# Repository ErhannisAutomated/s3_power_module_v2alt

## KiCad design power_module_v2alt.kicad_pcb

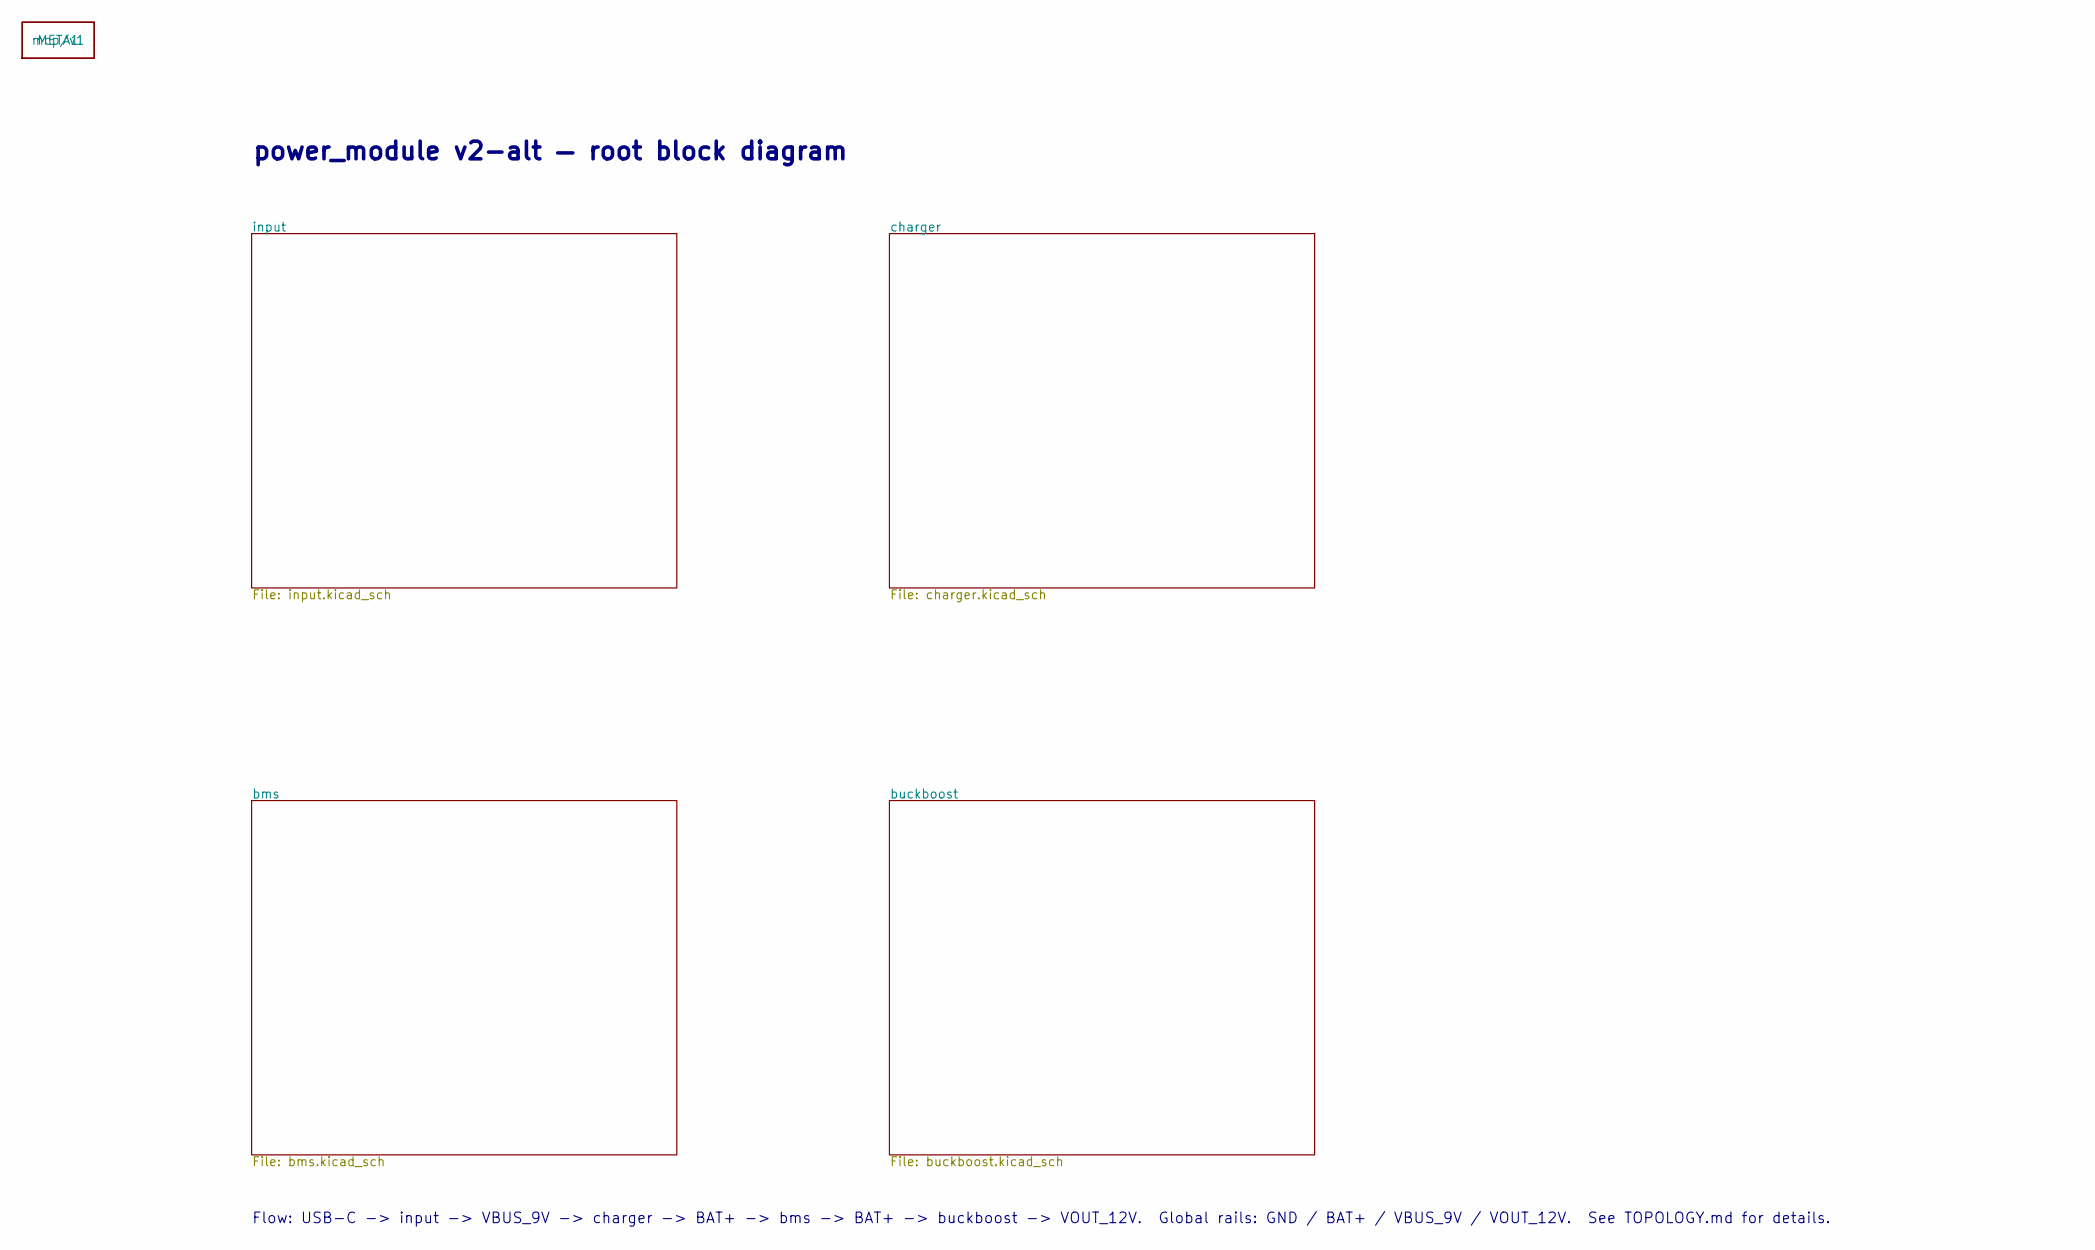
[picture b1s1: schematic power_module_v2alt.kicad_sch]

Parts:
META1: mcp/v1

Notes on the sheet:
power_module v2-alt — root block diagram
Flow: USB-C -> input -> VBUS_9V -> charger -> BAT+ -> bms -> BAT+ -> buckboost -> VOUT_12V. Global rails: GND / BAT+ / VBUS_9V / VOUT_12V. See TOPOLOGY.md for details.

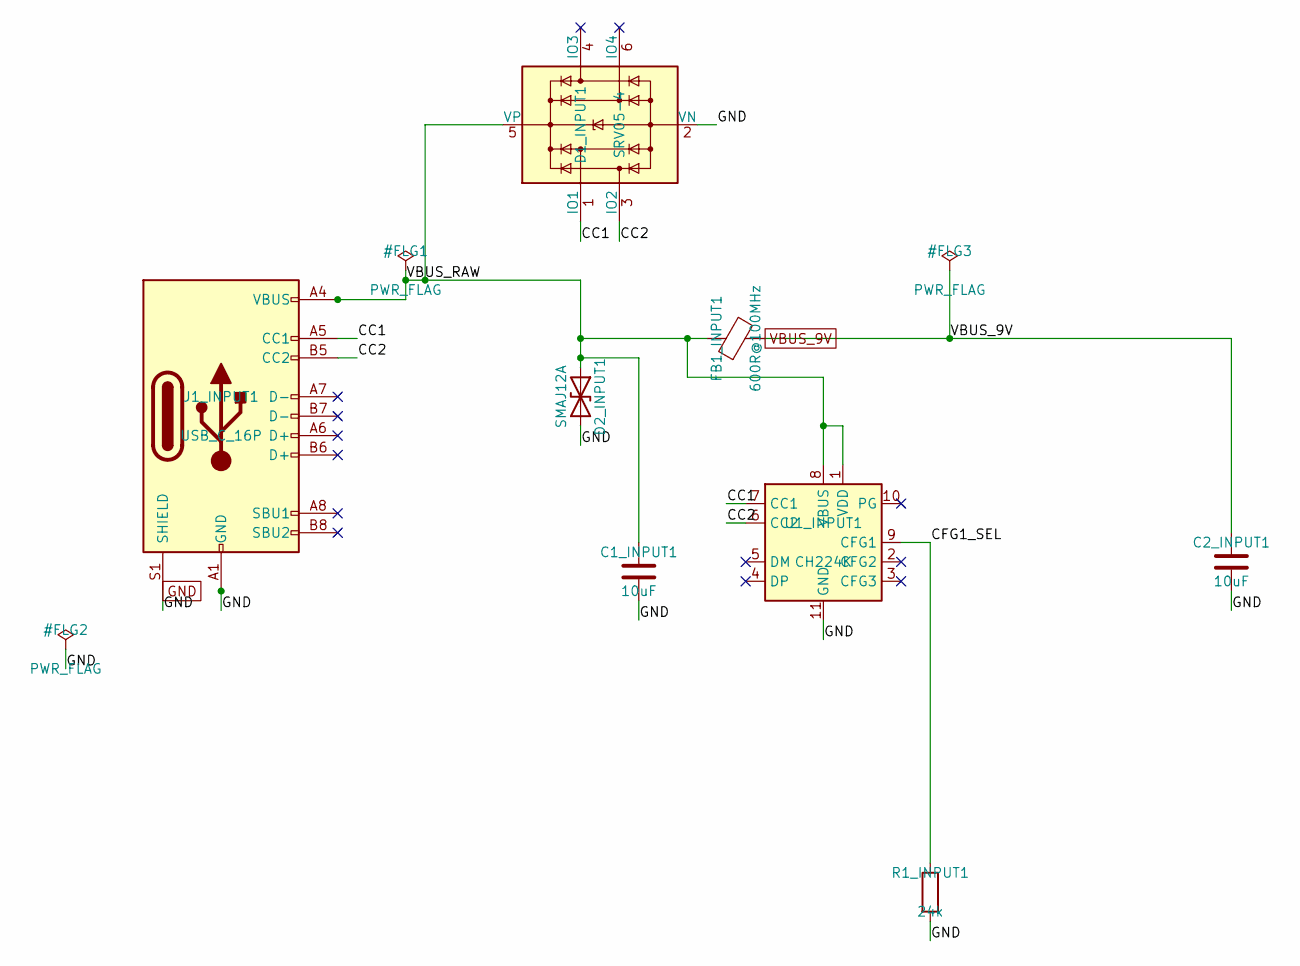
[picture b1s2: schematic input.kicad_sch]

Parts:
C1_INPUT1, C2_INPUT1: 10uF; C_0805_2012Metric; MPN CL21A106KAYNNNE; LCSC C15850
D1_INPUT1: SRV05-4; SOT-23-6; MPN SRV05-4; LCSC C7420376
D2_INPUT1: SMAJ12A; D_SMA; MPN SMAJ12A; LCSC C19077531
FB1_INPUT1: 600R@100MHz; L_0603_1608Metric; MPN CBW160808U601T; LCSC C139183
J1_INPUT1: USB_C_16P; USB_C_Receptacle_HRO_TYPE-C-31-M-12; MPN KH-TYPE-C-16P; LCSC C709357
R1_INPUT1: 24k; R_0603_1608Metric; MPN 0603WAF2402T5E; LCSC C23352
U1_INPUT1: CH224K; SSOP-10-1EP_3.9x4.9mm_P1mm_EP2.1x3.3mm; MPN CH224K; LCSC C970725

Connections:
CC1: D1_INPUT1.1 (IO1), J1_INPUT1.A5 (CC1), U1_INPUT1.7 (CC1)
CC2: D1_INPUT1.3 (IO2), J1_INPUT1.B5 (CC2), U1_INPUT1.6 (CC2)
CFG1_SEL: R1_INPUT1.1, U1_INPUT1.9 (CFG1)
GND: C1_INPUT1.2, C2_INPUT1.2, D1_INPUT1.2 (VN), D2_INPUT1.2 (A2), J1_INPUT1.A1 (GND), J1_INPUT1.A12 (GND), J1_INPUT1.B1 (GND), J1_INPUT1.B12 (GND), J1_INPUT1.S1 (SHIELD), R1_INPUT1.2, U1_INPUT1.11 (GND); also elsewhere on the board
VBUS_9V: C2_INPUT1.1, FB1_INPUT1.2; also elsewhere on the board
VBUS_RAW: C1_INPUT1.1, D1_INPUT1.5 (VP), D2_INPUT1.1 (A1), FB1_INPUT1.1, J1_INPUT1.A4 (VBUS), J1_INPUT1.A9 (VBUS), J1_INPUT1.B4 (VBUS), J1_INPUT1.B9 (VBUS), U1_INPUT1.1 (VDD), U1_INPUT1.8 (VBUS)

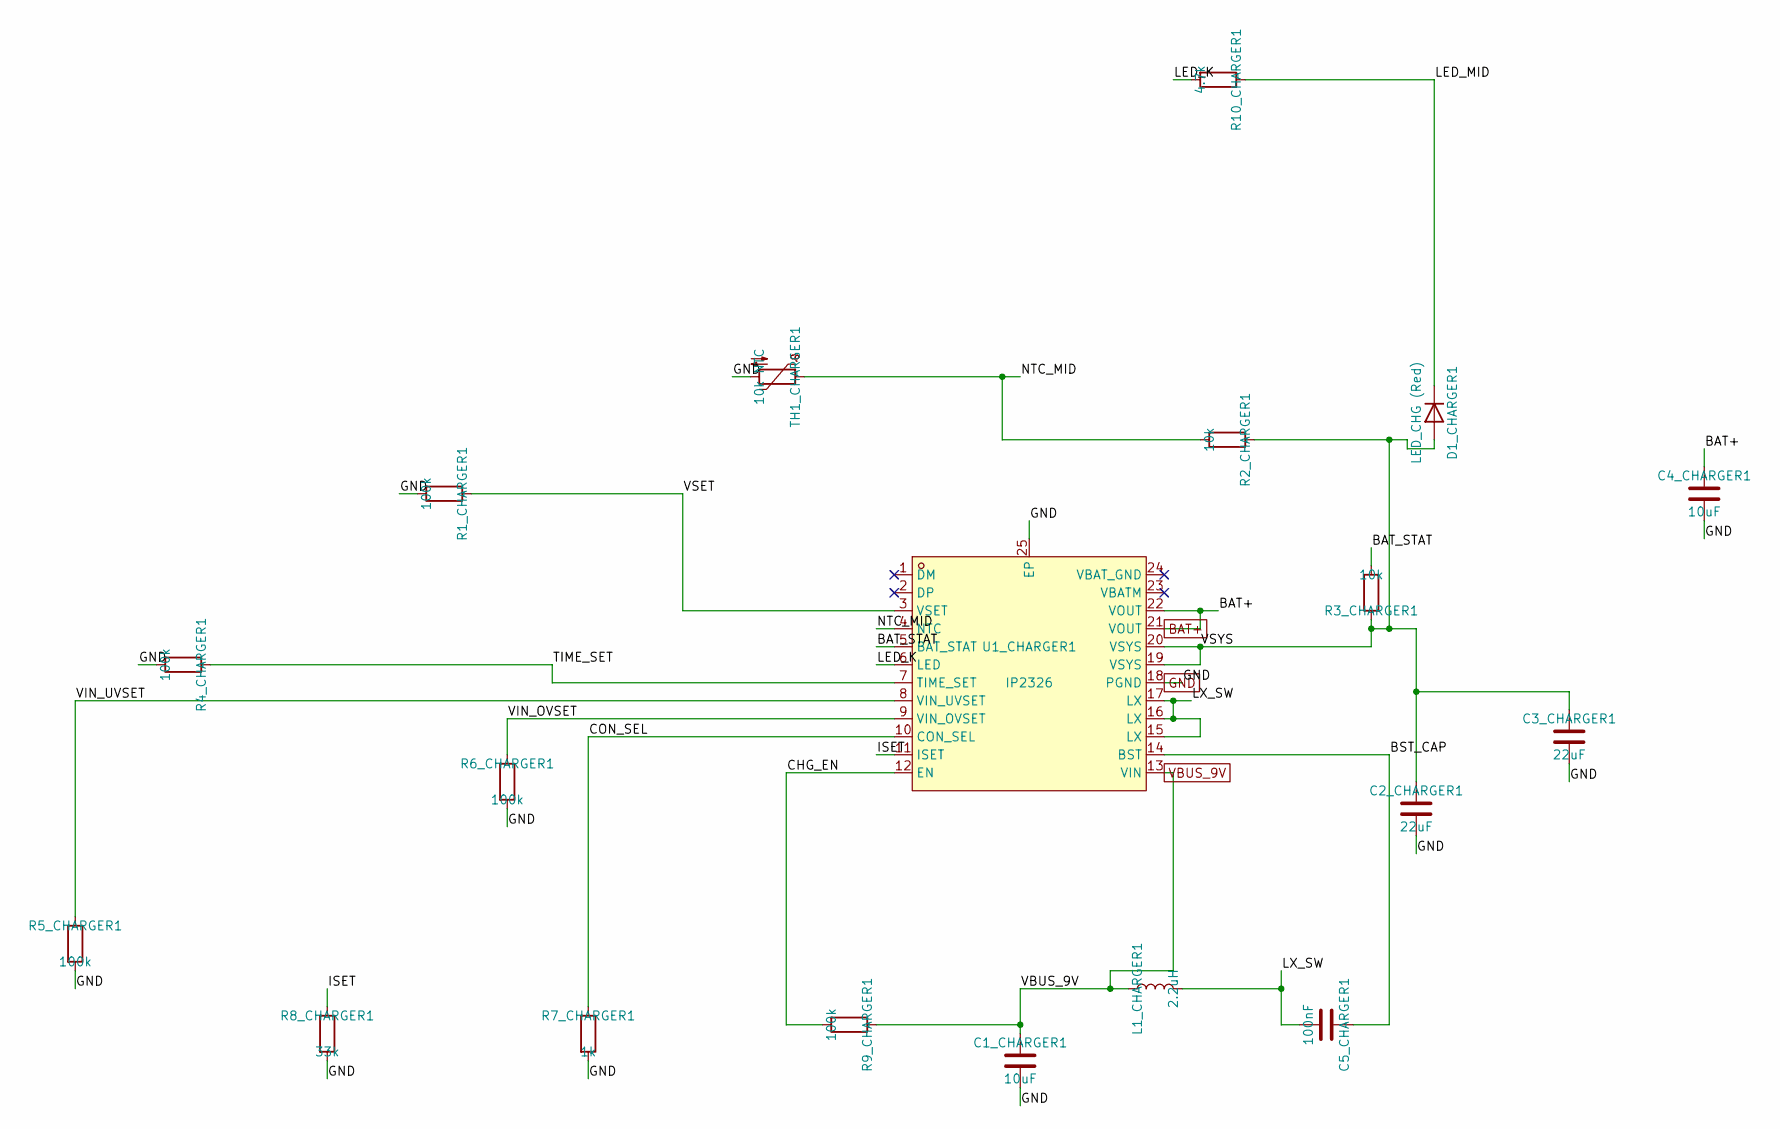
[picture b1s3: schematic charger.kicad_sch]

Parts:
C1_CHARGER1, C4_CHARGER1: 10uF; C_0805_2012Metric; MPN CL21A106KAYNNNE; LCSC C15850
C2_CHARGER1, C3_CHARGER1: 22uF; C_0805_2012Metric; MPN CL21A226MAQNNNE; LCSC C45783
C5_CHARGER1: 100nF; C_0603_1608Metric; MPN CC0603KRX7R9BB104; LCSC C14663
D1_CHARGER1: LED_CHG (Red); LED_0603_1608Metric; MPN KT-0603R; LCSC C2286
L1_CHARGER1: 2.2uH; L_Sunlord_MWSA0402S; MPN FHD4020S-2R2MT; LCSC C602029
R1_CHARGER1, R4_CHARGER1, R5_CHARGER1, R6_CHARGER1, R9_CHARGER1: 100k; R_0603_1608Metric; MPN 0603WAF1003T5E; LCSC C25803
R2_CHARGER1, R3_CHARGER1: 10k; R_0603_1608Metric; MPN 0603WAF1002T5E; LCSC C25804
R7_CHARGER1: 1k; R_0603_1608Metric; MPN 0603WAF1001T5E; LCSC C21190
R8_CHARGER1: 33k; R_0603_1608Metric; MPN 0603WAF3302T5E; LCSC C4216
R10_CHARGER1: 4.7k; R_0603_1608Metric; MPN 0603WAF4701T5E; LCSC C23162
TH1_CHARGER1: 10k NTC; R_0603_1608Metric; MPN CMFA 103F3435; LCSC C2889048
U1_CHARGER1: IP2326; VQFN-24_L4.0-W4.0-P0.50-BL-EP2.5; MPN IP2326; LCSC C2832094

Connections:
BAT+: C4_CHARGER1.1, U1_CHARGER1.21 (VOUT), U1_CHARGER1.22 (VOUT); also elsewhere on the board
BAT_STAT: R3_CHARGER1.2, U1_CHARGER1.5 (BAT_STAT)
BST_CAP: C5_CHARGER1.1, U1_CHARGER1.14 (BST)
CHG_EN: R9_CHARGER1.2, U1_CHARGER1.12 (EN)
CON_SEL: R7_CHARGER1.1, U1_CHARGER1.10 (CON_SEL)
GND: C1_CHARGER1.2, C2_CHARGER1.2, C3_CHARGER1.2, C4_CHARGER1.2, R1_CHARGER1.2, R4_CHARGER1.2, R5_CHARGER1.2, R6_CHARGER1.2, R7_CHARGER1.2, R8_CHARGER1.2, TH1_CHARGER1.2, U1_CHARGER1.18 (PGND), U1_CHARGER1.25 (EP); also elsewhere on the board
ISET: R8_CHARGER1.1, U1_CHARGER1.11 (ISET)
LED_K: R10_CHARGER1.2, U1_CHARGER1.6 (LED)
LED_MID: D1_CHARGER1.1 (K), R10_CHARGER1.1
LX_SW: C5_CHARGER1.2, L1_CHARGER1.2, U1_CHARGER1.15 (LX), U1_CHARGER1.16 (LX), U1_CHARGER1.17 (LX)
NTC_MID: R2_CHARGER1.2, TH1_CHARGER1.1, U1_CHARGER1.4 (NTC)
TIME_SET: R4_CHARGER1.1, U1_CHARGER1.7 (TIME_SET)
VBUS_9V: C1_CHARGER1.1, L1_CHARGER1.1, R9_CHARGER1.1, U1_CHARGER1.13 (VIN); also elsewhere on the board
VIN_OVSET: R6_CHARGER1.1, U1_CHARGER1.9 (VIN_OVSET)
VIN_UVSET: R5_CHARGER1.1, U1_CHARGER1.8 (VIN_UVSET)
VSET: R1_CHARGER1.1, U1_CHARGER1.3 (VSET)
VSYS: C2_CHARGER1.1, C3_CHARGER1.1, D1_CHARGER1.2 (A), R2_CHARGER1.1, R3_CHARGER1.1, U1_CHARGER1.19 (VSYS), U1_CHARGER1.20 (VSYS)

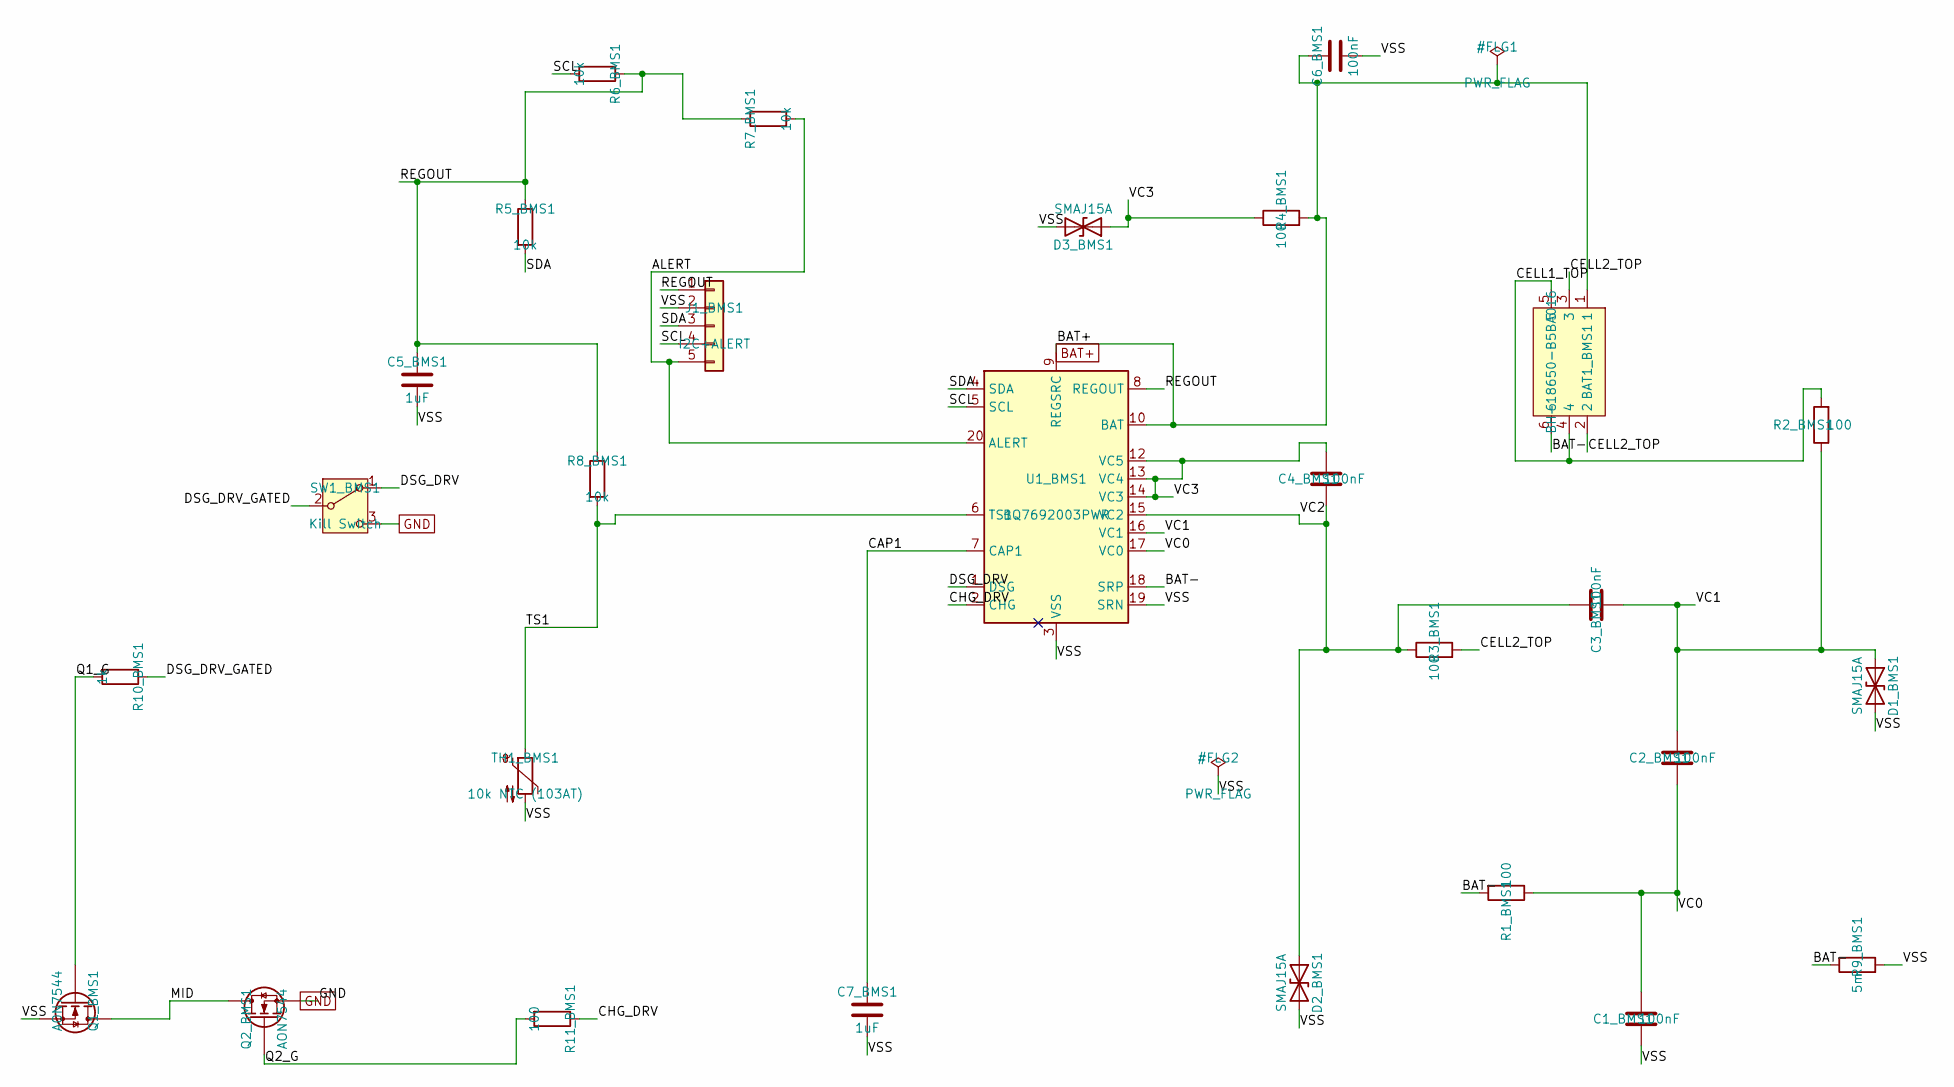
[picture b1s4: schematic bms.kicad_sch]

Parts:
BAT1_BMS1: BH-18650-B5BA016; BAT-SMD_BH-18650-B5BA016; MPN BH-18650-B5BA016; LCSC C19184086
C1_BMS1, C2_BMS1, C3_BMS1, C4_BMS1, C6_BMS1: 100nF; C_0603_1608Metric; MPN CC0603KRX7R9BB104; LCSC C14663
C5_BMS1, C7_BMS1: 1uF; C_0603_1608Metric; MPN CL10A105KB8NNNC; LCSC C15849
D1_BMS1, D2_BMS1, D3_BMS1: SMAJ15A; D_SMA; MPN SMAJ15A; LCSC C19077535
J1_BMS1: I2C+ALERT; PinHeader_1x05_P2.54mm_Vertical; MPN PZ254V-11-05P; LCSC C492404
Q1_BMS1, Q2_BMS1: AON7544; DFN-8_L3.3-W3.3-P0.65-BL-2; MPN AON7544; LCSC C315567
R1_BMS1, R2_BMS1, R3_BMS1, R4_BMS1, R11_BMS1: 100; R_0603_1608Metric; MPN 0603WAF1000T5E; LCSC C22775
R5_BMS1, R6_BMS1, R7_BMS1, R8_BMS1: 10k; R_0603_1608Metric; MPN 0603WAF1002T5E; LCSC C25804
R9_BMS1: 5m; R_2512_6332Metric; MPN RLM25FEER005; LCSC C185817
R10_BMS1: 1k; R_0603_1608Metric; MPN 0603WAF1001T5E; LCSC C21190
SW1_BMS1: Kill Switch; SW_SPDT_PCM12
TH1_BMS1: 10k NTC (103AT); R_0603_1608Metric; MPN CMFA 103F3435; LCSC C2889048
U1_BMS1: BQ7692003PWR; TSSOP-20_4.4x6.5mm_P0.65mm; MPN BQ7692003PWR; LCSC C601650

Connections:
ALERT: J1_BMS1.5, R7_BMS1.2, U1_BMS1.20 (ALERT)
BAT+: BAT1_BMS1.1, C6_BMS1.1, R4_BMS1.2, U1_BMS1.9 (REGSRC), U1_BMS1.10 (BAT); also elsewhere on the board
BAT-: BAT1_BMS1.6, R1_BMS1.2, R9_BMS1.1, U1_BMS1.18 (SRP)
CAP1: C7_BMS1.1, U1_BMS1.7 (CAP1)
CELL1_TOP: BAT1_BMS1.4, BAT1_BMS1.5, R2_BMS1.2
CELL2_TOP: BAT1_BMS1.2, BAT1_BMS1.3, R3_BMS1.2
CHG_DRV: R11_BMS1.1, U1_BMS1.2 (CHG)
DSG_DRV: SW1_BMS1.1 (A), U1_BMS1.1 (DSG)
DSG_DRV_GATED: R10_BMS1.1, SW1_BMS1.2 (B)
GND: Q2_BMS1.S, SW1_BMS1.3 (C); also elsewhere on the board
MID: Q1_BMS1.D, Q2_BMS1.D
Q1_G: Q1_BMS1.G, R10_BMS1.2
Q2_G: Q2_BMS1.G, R11_BMS1.2
REGOUT: C5_BMS1.1, J1_BMS1.1, R5_BMS1.1, R6_BMS1.1, R7_BMS1.1, R8_BMS1.1, U1_BMS1.8 (REGOUT)
SCL: J1_BMS1.4, R6_BMS1.2, U1_BMS1.5 (SCL)
SDA: J1_BMS1.3, R5_BMS1.2, U1_BMS1.4 (SDA)
TS1: R8_BMS1.2, TH1_BMS1.1, U1_BMS1.6 (TS1)
VC0: C1_BMS1.2, C2_BMS1.1, R1_BMS1.1, U1_BMS1.17 (VC0)
VC1: C2_BMS1.2, C3_BMS1.1, D1_BMS1.1 (A1), R2_BMS1.1, U1_BMS1.16 (VC1)
VC2: C3_BMS1.2, C4_BMS1.1, D2_BMS1.1 (A1), R3_BMS1.1, U1_BMS1.15 (VC2)
VC3: C4_BMS1.2, D3_BMS1.1 (A1), R4_BMS1.1, U1_BMS1.12 (VC5), U1_BMS1.13 (VC4), U1_BMS1.14 (VC3)
VSS: C1_BMS1.1, C5_BMS1.2, C6_BMS1.2, C7_BMS1.2, D1_BMS1.2 (A2), D2_BMS1.2 (A2), D3_BMS1.2 (A2), J1_BMS1.2, Q1_BMS1.S, R9_BMS1.2, TH1_BMS1.2, U1_BMS1.3 (VSS), U1_BMS1.19 (SRN)

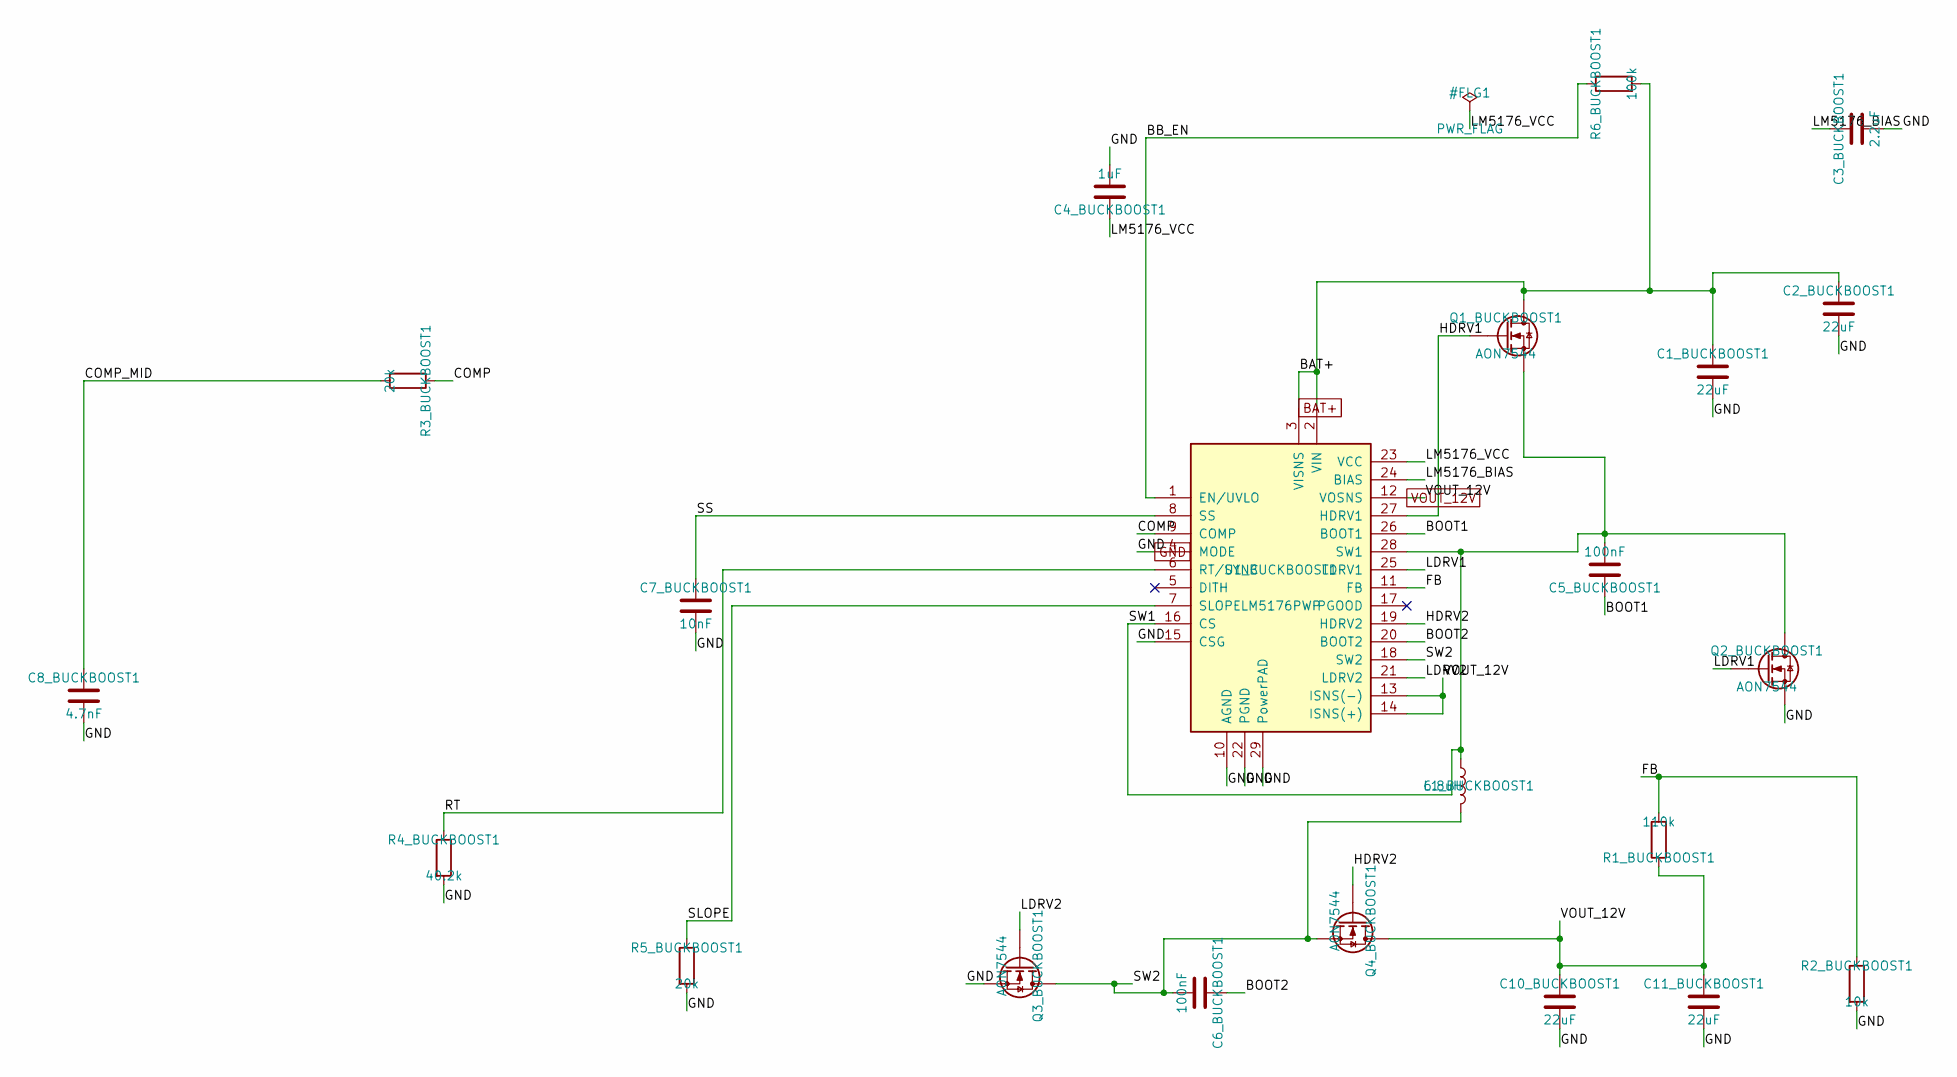
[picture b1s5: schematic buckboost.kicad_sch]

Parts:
C1_BUCKBOOST1, C2_BUCKBOOST1, C10_BUCKBOOST1, C11_BUCKBOOST1: 22uF; C_0805_2012Metric; MPN CL21A226MAQNNNE; LCSC C45783
C3_BUCKBOOST1: 2.2uF; C_0603_1608Metric; MPN CL10A225KO8NNNC; LCSC C23630
C4_BUCKBOOST1: 1uF; C_0603_1608Metric; MPN CL10A105KB8NNNC; LCSC C15849
C5_BUCKBOOST1, C6_BUCKBOOST1: 100nF; C_0603_1608Metric; MPN CC0603KRX7R9BB104; LCSC C14663
C7_BUCKBOOST1: 10nF; C_0603_1608Metric; MPN FCC0603B103K500CT; LCSC C5137477
C8_BUCKBOOST1: 4.7nF; C_0603_1608Metric; MPN 0603B472K500NT; LCSC C53987
L1_BUCKBOOST1: 6.8uH; L_Sumida_CDMC6D28_7.25x6.5mm; MPN FXL0630-6R8-M; LCSC C167221
Q1_BUCKBOOST1, Q2_BUCKBOOST1, Q3_BUCKBOOST1, Q4_BUCKBOOST1: AON7544; DFN-8_L3.3-W3.3-P0.65-BL-2; MPN AON7544; LCSC C315567
R1_BUCKBOOST1: 110k; R_0603_1608Metric; MPN 0603WAF1103T5E; LCSC C25805
R2_BUCKBOOST1: 10k; R_0603_1608Metric; MPN 0603WAF1002T5E; LCSC C25804
R3_BUCKBOOST1, R5_BUCKBOOST1: 20k; R_0603_1608Metric; MPN 0603WAF2002T5E; LCSC C4184
R4_BUCKBOOST1: 40.2k; R_0603_1608Metric; MPN 0603WAF4022T5E; LCSC C12447
R6_BUCKBOOST1: 100k; R_0603_1608Metric; MPN 0603WAF1003T5E; LCSC C25803
U1_BUCKBOOST1: LM5176PWP; HTSSOP-28-1EP_4.4x9.7mm_P0.65mm_EP3.4x9.5mm_ThermalVias; MPN LM5176PWPR; LCSC C442493

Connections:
BAT+: C1_BUCKBOOST1.1, C2_BUCKBOOST1.1, Q1_BUCKBOOST1.D, R6_BUCKBOOST1.2, U1_BUCKBOOST1.2 (VIN), U1_BUCKBOOST1.3 (VISNS); also elsewhere on the board
BB_EN: R6_BUCKBOOST1.1, U1_BUCKBOOST1.1 (EN/UVLO)
BOOT1: C5_BUCKBOOST1.1, U1_BUCKBOOST1.26 (BOOT1)
BOOT2: C6_BUCKBOOST1.1, U1_BUCKBOOST1.20 (BOOT2)
COMP: R3_BUCKBOOST1.1, U1_BUCKBOOST1.9 (COMP)
COMP_MID: C8_BUCKBOOST1.1, R3_BUCKBOOST1.2
FB: R1_BUCKBOOST1.2, R2_BUCKBOOST1.1, U1_BUCKBOOST1.11 (FB)
GND: C1_BUCKBOOST1.2, C2_BUCKBOOST1.2, C3_BUCKBOOST1.2, C4_BUCKBOOST1.2, C7_BUCKBOOST1.2, C8_BUCKBOOST1.2, C10_BUCKBOOST1.2, C11_BUCKBOOST1.2, Q2_BUCKBOOST1.S, Q3_BUCKBOOST1.S, R2_BUCKBOOST1.2, R4_BUCKBOOST1.2, R5_BUCKBOOST1.2, U1_BUCKBOOST1.4 (MODE), U1_BUCKBOOST1.10 (AGND), U1_BUCKBOOST1.15 (CSG), U1_BUCKBOOST1.22 (PGND), U1_BUCKBOOST1.29 (PowerPAD); also elsewhere on the board
HDRV1: Q1_BUCKBOOST1.G, U1_BUCKBOOST1.27 (HDRV1)
HDRV2: Q4_BUCKBOOST1.G, U1_BUCKBOOST1.19 (HDRV2)
LDRV1: Q2_BUCKBOOST1.G, U1_BUCKBOOST1.25 (LDRV1)
LDRV2: Q3_BUCKBOOST1.G, U1_BUCKBOOST1.21 (LDRV2)
LM5176_BIAS: C3_BUCKBOOST1.1, U1_BUCKBOOST1.24 (BIAS)
LM5176_VCC: C4_BUCKBOOST1.1, U1_BUCKBOOST1.23 (VCC)
RT: R4_BUCKBOOST1.1, U1_BUCKBOOST1.6 (RT/SYNC)
SLOPE: R5_BUCKBOOST1.1, U1_BUCKBOOST1.7 (SLOPE)
SS: C7_BUCKBOOST1.1, U1_BUCKBOOST1.8 (SS)
SW1: C5_BUCKBOOST1.2, L1_BUCKBOOST1.1, Q1_BUCKBOOST1.S, Q2_BUCKBOOST1.D, U1_BUCKBOOST1.16 (CS), U1_BUCKBOOST1.28 (SW1)
SW2: C6_BUCKBOOST1.2, L1_BUCKBOOST1.2, Q3_BUCKBOOST1.D, Q4_BUCKBOOST1.S, U1_BUCKBOOST1.18 (SW2)
VOUT_12V: C10_BUCKBOOST1.1, C11_BUCKBOOST1.1, Q4_BUCKBOOST1.D, R1_BUCKBOOST1.1, U1_BUCKBOOST1.12 (VOSNS), U1_BUCKBOOST1.13 (ISNS(-)), U1_BUCKBOOST1.14 (ISNS(+))

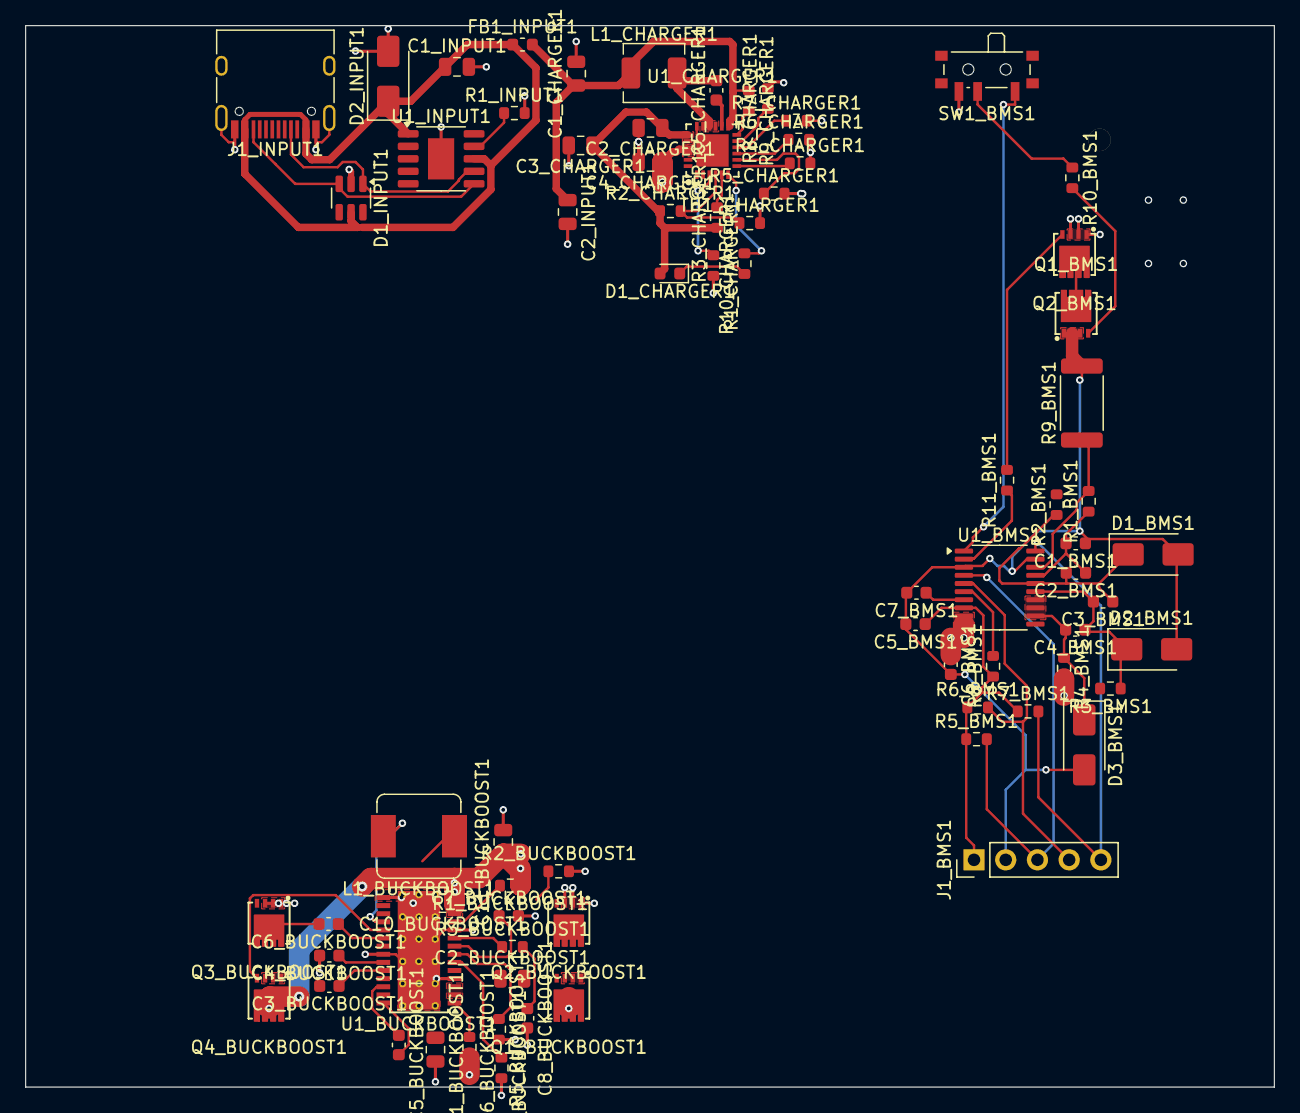
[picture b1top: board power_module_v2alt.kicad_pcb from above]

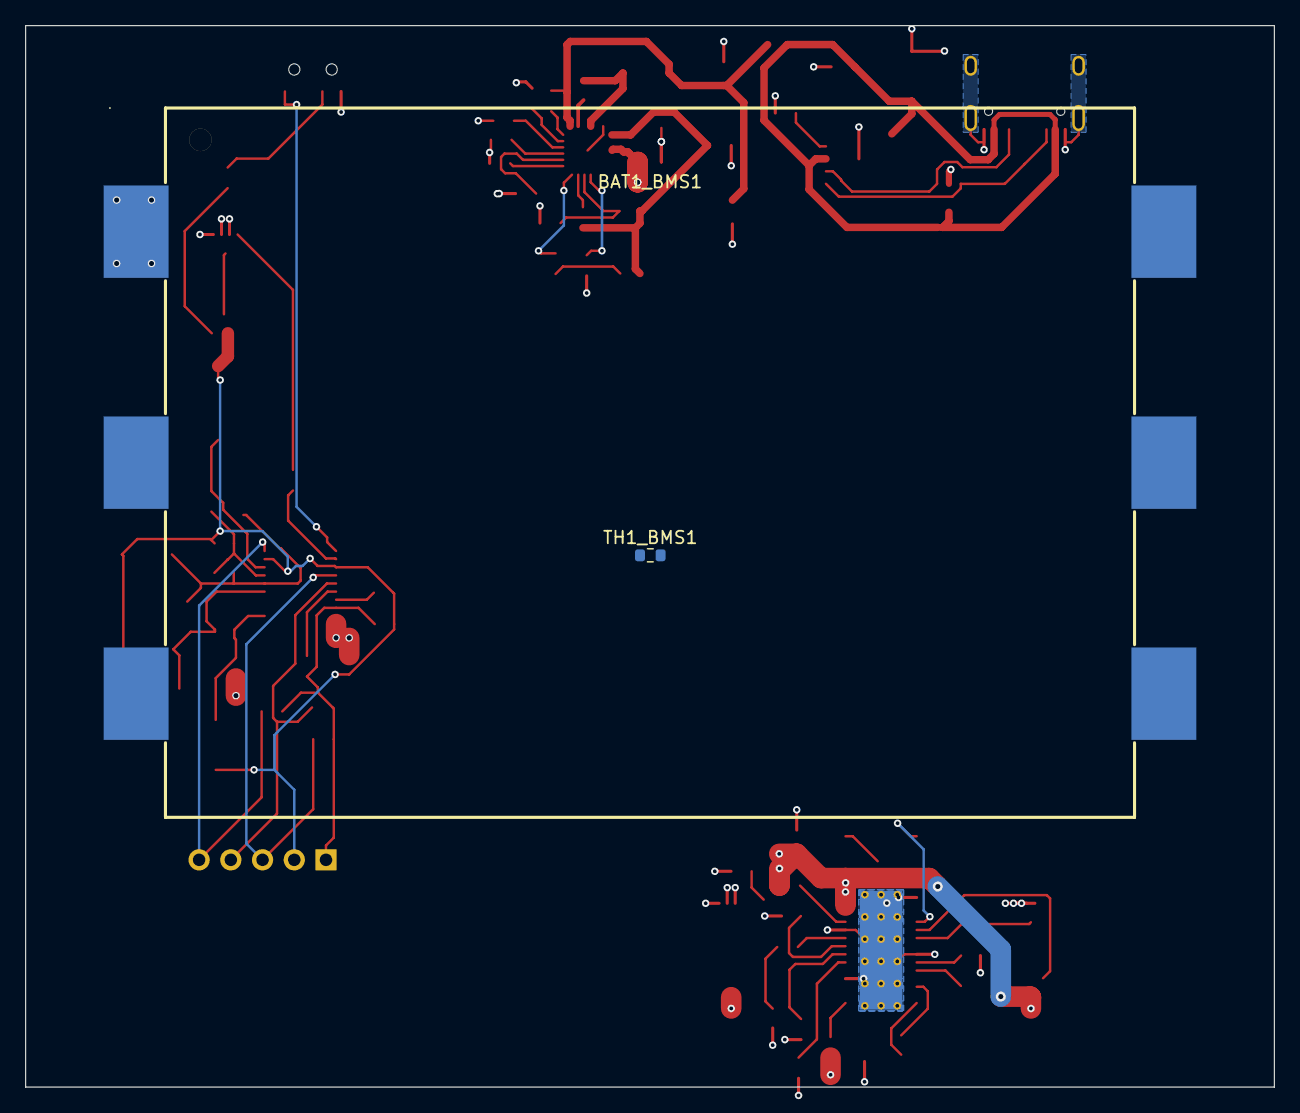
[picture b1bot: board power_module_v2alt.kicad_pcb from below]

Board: 4 copper layers, 100.0 x 85.0 mm, 77 parts (2 on the bottom side), 59 nets.
